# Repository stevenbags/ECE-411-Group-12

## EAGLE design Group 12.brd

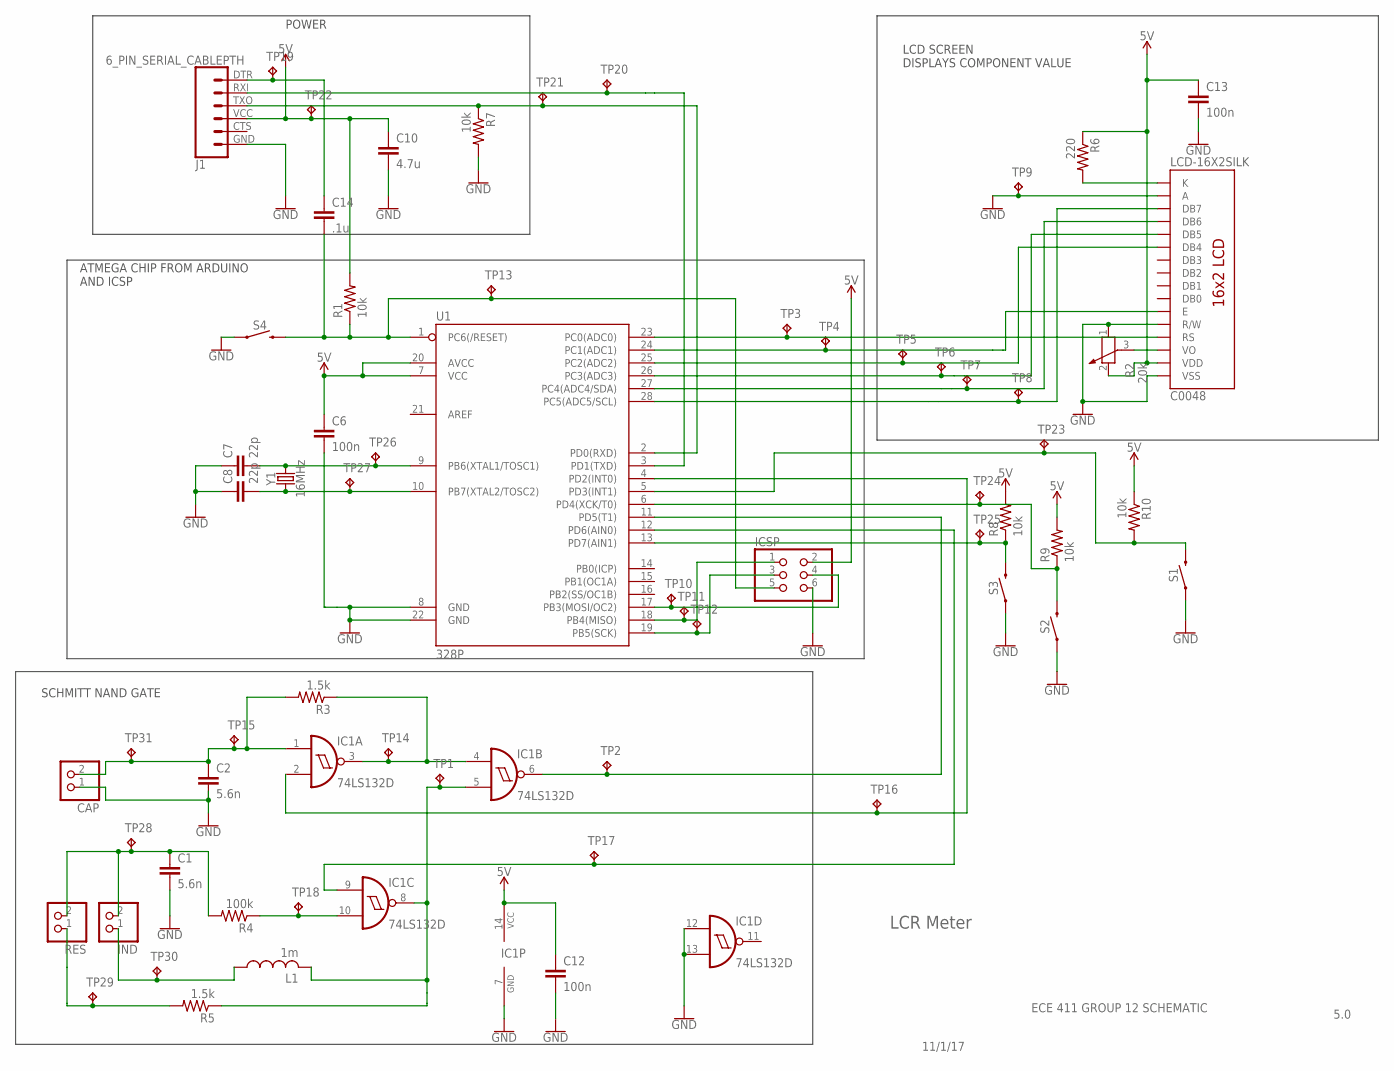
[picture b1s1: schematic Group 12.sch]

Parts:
C1, C2: 5.6n; C0805K
C6, C12, C13: 100n; C0805K
C7, C8: 22p; C0805K
C10: 4.7u; C0805K
C14: .1u; C0805K
C0048: LCD-16X2SILK; LCD-16X2
CAP: PINHD-1X2; 1X02
IC1: 74LS132D; SO14
ICSP: PINHD-2X3; 2X03
IND: PINHD-1X2; 1X02
J1: 6_PIN_SERIAL_CABLEPTH; FTDI_BASIC
L1: 1m; 0204/5
R1, R7, R8, R9, R10: 10k; R0805
R2: 20k; PT-10
R3, R5: 1.5k; M0805
R4: 100k; M0805
R6: 220; R0805
RES: PINHD-1X2; 1X02
S1, S2, S3, S4: MOMENTARY-SWITCH-SPST-SMD-6.0X3.5MM; TACTILE_SWITCH_SMD_6.0X3.5MM
TP1, TP2, TP3, TP4, TP5, TP6, TP7, TP8, TP9, TP10, TP11, TP12, TP13, TP14, TP15, TP16, TP17, TP18, TP19, TP20, TP21, TP22, TP23, TP24, TP25, TP26, TP27, TP28, TP29, TP30, TP31: TPPAD1-13; P1-13
U1: 328P; DIP28
Y1: 16MHz; CRYSTAL-SMD-5X3.2-4PAD

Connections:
5V: C6.1, C10.1, C12.1, C13.1, C0048.2 (VDD), IC1.14 (VCC), ICSP.2, J1.VCC (4), R1.2, R2.2, R6.1, R8.2, R9.2, R10.1, TP22.TP, U1.7 (VCC), U1.20 (AVCC)
CAL: R9.1, S2.2, TP24.TP, U1.6 (PD4(XCK/T0))
GND: C1.2, C2.2, C6.2, C7.1, C8.1, C10.2, C12.2, C13.2, C0048.1 (VSS), C0048.5 (R/W), C0048.15 (A), CAP.1, IC1.7 (GND), IC1.12 (I0), IC1.13 (I1), ICSP.6, J1.GND (6), R2.1, R7.2, S1.1, S2.1, S3.1, S4.1, TP9.TP, U1.8 (GND), U1.22 (GND)
MISO: ICSP.1, TP11.TP, U1.18 (PB4(MISO))
MODE: R10.2, S1.2, TP23.TP, U1.5 (PD3(INT1))
unnamed: C2.1, CAP.2, IC1.1 (I0), R3.2, TP15.TP, TP31.TP
unnamed: IC1.10 (I1), R4.1, TP18.TP
unnamed: J1.RXI (2), TP20.TP, U1.3 (PD1(TXD))
unnamed: ICSP.4, TP10.TP, U1.17 (PB3(MOSI/OC2))
unnamed: IC1.3 (O), IC1.4 (I0), R3.1, TP14.TP
unnamed: C14.1, J1.DTR (1), TP19.TP
unnamed: R5.2, RES.1, TP29.TP
unnamed: IC1.5 (I1), IC1.8 (O), L1.2, R5.1, TP1.TP
unnamed: IND.1, L1.1, TP30.TP
unnamed: C1.1, IND.2, R4.2, RES.2, TP28.TP
unnamed: C0048.3 (VO), R2.3
unnamed: C0048.16 (K), R6.2
PB6: C7.2, TP26.TP, U1.9 (PB6(XTAL1/TOSC1)), Y1.3 (2)
PB7: C8.2, TP27.TP, U1.10 (PB7(XTAL2/TOSC2)), Y1.1
PC0: C0048.4 (RS), TP3.TP, U1.23 (PC0(ADC0))
PC1: C0048.6 (E), TP4.TP, U1.24 (PC1(ADC1))
PC2: C0048.11 (DB4), TP5.TP, U1.25 (PC2(ADC2))
PC3: C0048.12 (DB5), TP6.TP, U1.26 (PC3(ADC3))
PC4: C0048.13 (DB6), TP7.TP, U1.27 (PC4(ADC4/SDA))
PC5: C0048.14 (DB7), TP8.TP, U1.28 (PC5(ADC5/SCL))
PD0: J1.TXO (3), R7.1, TP21.TP, U1.2 (PD0(RXD))
PD2: IC1.2 (I1), TP16.TP, U1.4 (PD2(INT0))
PD5: IC1.6 (O), TP2.TP, U1.11 (PD5(T1))
PD6: IC1.9 (I0), TP17.TP, U1.12 (PD6(AIN0))
RESET: C14.2, ICSP.5, R1.1, S4.2, TP13.TP, U1.1 (PC6(/RESET))
SCK: ICSP.3, TP12.TP, U1.19 (PB5(SCK))
SET: R8.1, S3.2, TP25.TP, U1.13 (PD7(AIN1))

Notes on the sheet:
11/1/17
ECE 411 GROUP 12 SCHEMATIC
5.0
LCR Meter
POWER
LCD SCREEN DISPLAYS COMPONENT VALUE
ATMEGA CHIP FROM ARDUINO AND ICSP
SCHMITT NAND GATE

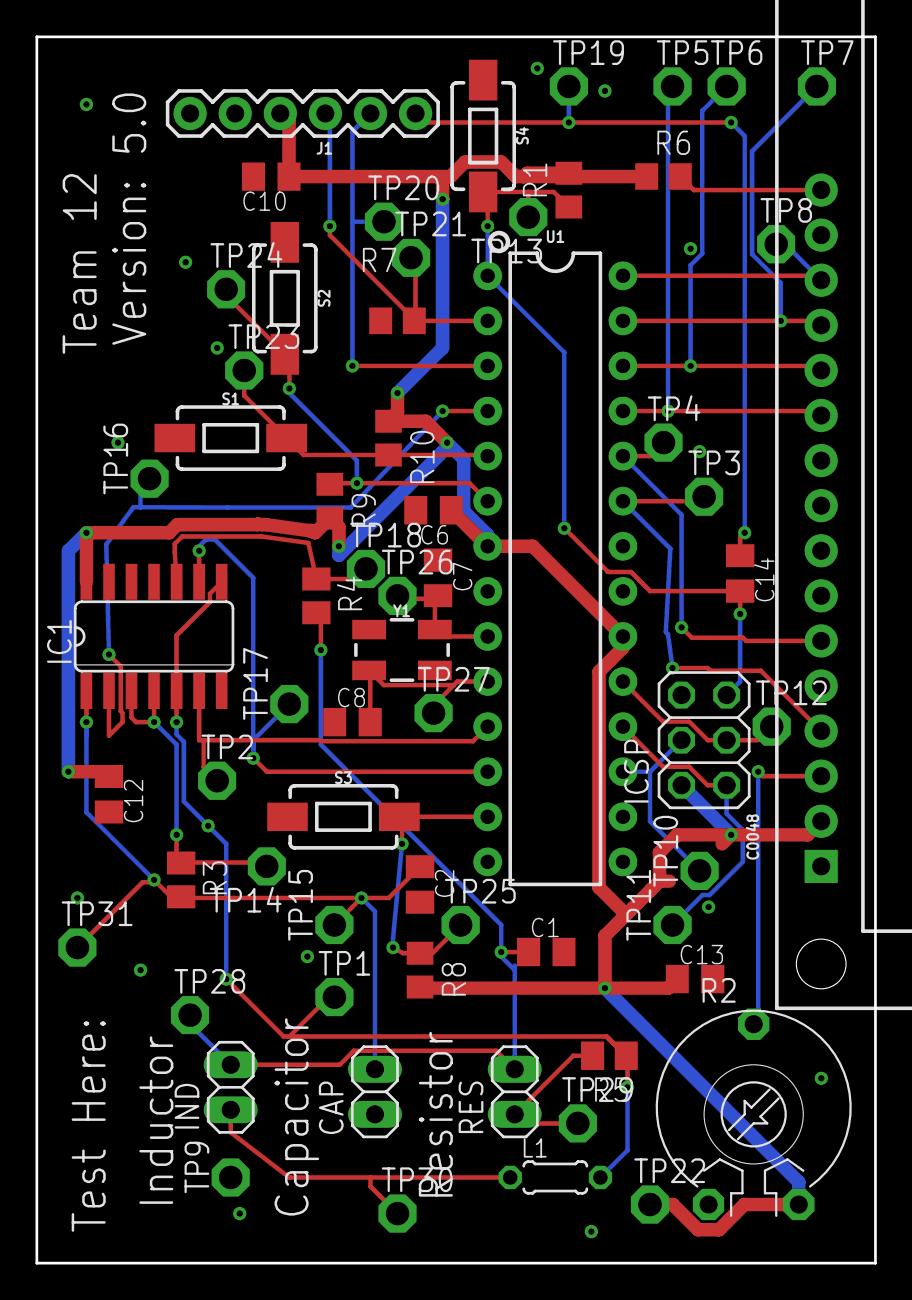
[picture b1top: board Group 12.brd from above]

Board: 2 copper layers, 47.2 x 69.1 mm, 64 parts (0 on the bottom side), 32 nets.

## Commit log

2017-10-25 Prelim Schem
    Prelim Schem
2017-11-02 Schm and Proj Sch
    Schematic and Project Schedule
2017-11-02 Final Schem
    Final Schem
2017-11-09 prelim layout
    prelim layout
2017-11-09 HW 5
    HW 5
2017-11-15 board and sch
    board and sch
2017-11-16 final sch and brd
    final sch and brd
2017-11-16 final brd and sch
    final brd and sch
2017-12-03 PDS v2
    PDS v2

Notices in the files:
parts and their libraries:
SparkFun-Displays: Licensing: Creative Commons ShareAlike 4.0 International - https://creativecommons.org/licenses/by-sa/4.0
